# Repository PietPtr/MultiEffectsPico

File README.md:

# mep

Experiments for building a multi-effects processor on a Raspberry Pi Pico using I2S ADC's / DAC's and other IO for configuration

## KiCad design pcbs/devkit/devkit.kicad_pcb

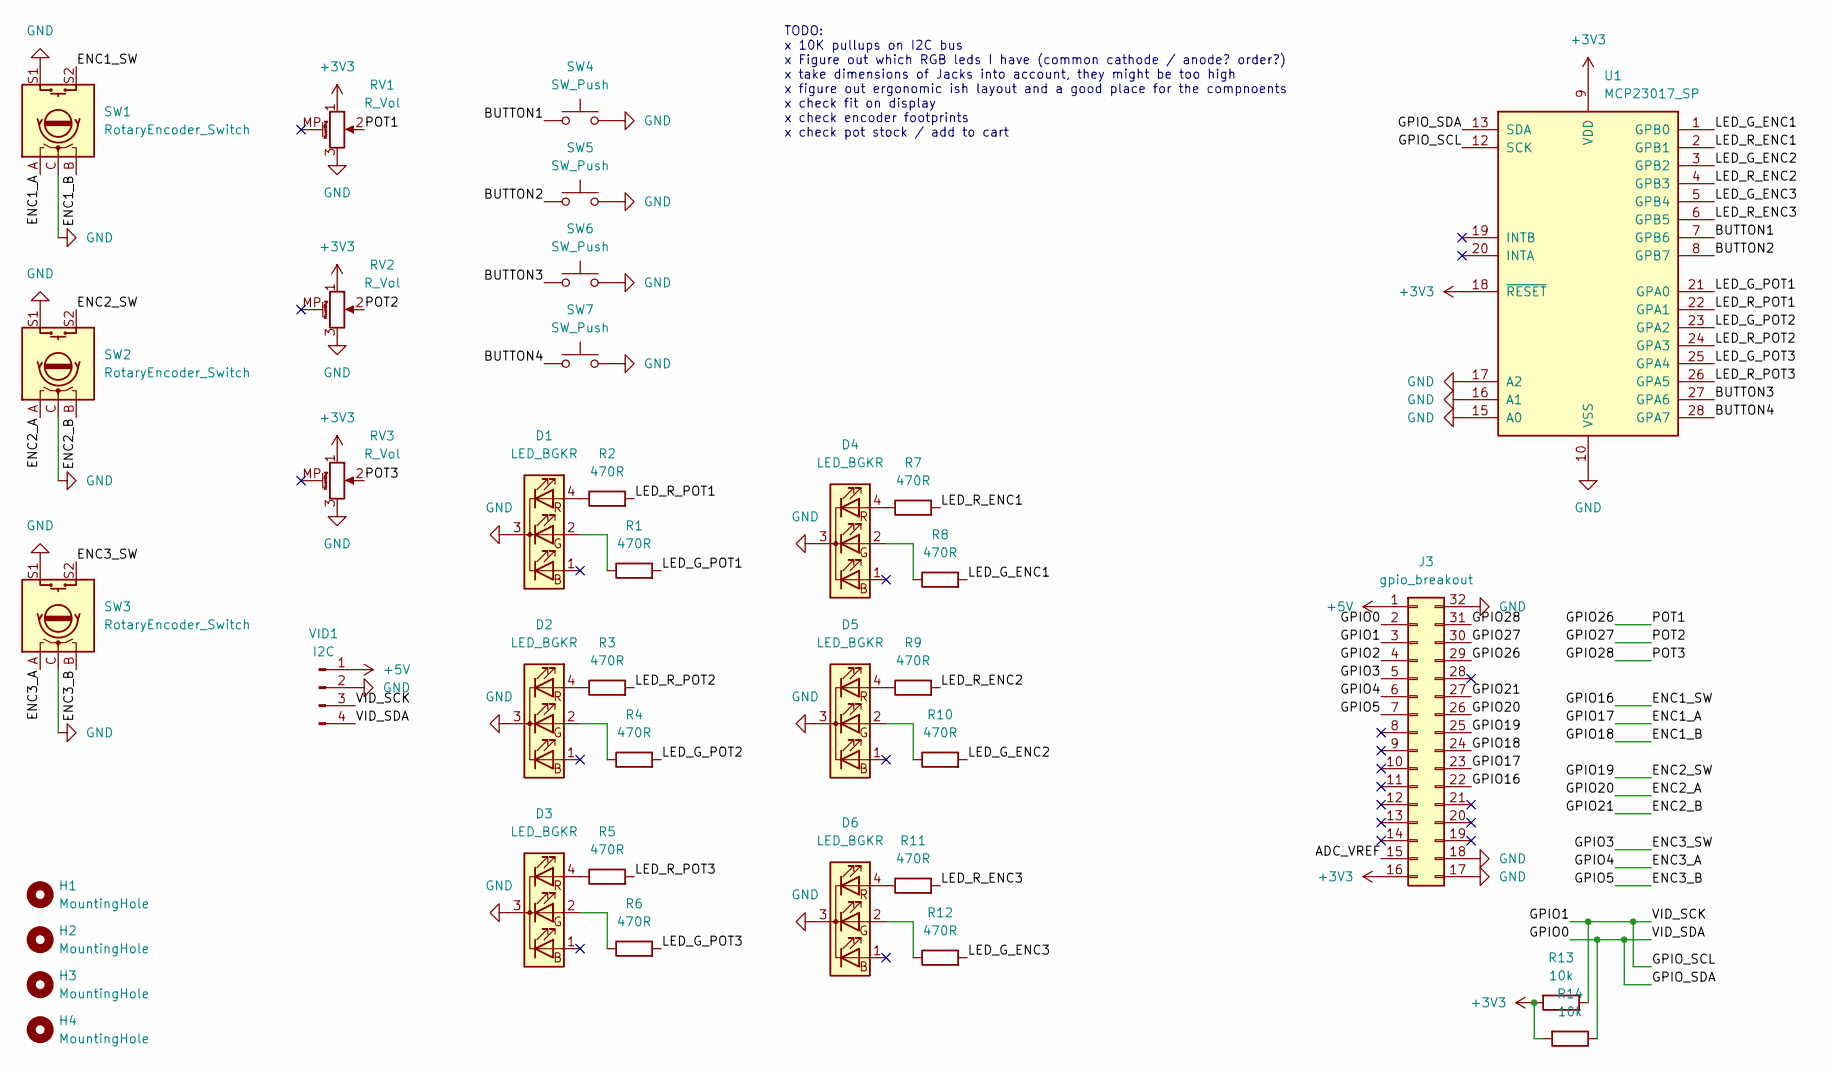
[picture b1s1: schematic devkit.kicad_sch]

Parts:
D1, D2, D3, D4, D5, D6: LED_BGKR; LED_D5.0mm-4_RGB
H1, H2, H3, H4: MountingHole; MountingHole_3.2mm_M3
J3: gpio_breakout; PinSocket_2x16_P2.54mm_Vertical
R1, R2, R3, R4, R5, R6, R7, R8, R9, R10, R11, R12: 470R; R_Axial_DIN0207_L6.3mm_D2.5mm_P7.62mm_Horizontal
R13, R14: 10k; R_Axial_DIN0207_L6.3mm_D2.5mm_P7.62mm_Horizontal
RV1, RV2, RV3: R_Vol; Potentiometer_Alps_RK09K_Single_Vertical
SW1, SW2, SW3: RotaryEncoder_Switch; RotaryEncoder_Alps_EC11E-Switch_Vertical_H20mm_MountingHoles
SW4, SW5, SW6, SW7: SW_Push; KAILH_MUTE
U1: MCP23017_SP; DIP-28_W7.62mm
VID1: I2C; PinHeader_1x04_P2.54mm_Vertical

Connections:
+3V3: J3.16, R13.2, R14.2, RV1.1, RV2.1, RV3.1, U1.9 (VDD), U1.18 (~RESET)
+5V: J3.1, VID1.1
/ADC_VREF: J3.15
/BUTTON1: SW4.1, U1.7 (GPB6)
/BUTTON2: SW5.1, U1.8 (GPB7)
/BUTTON3: SW6.1, U1.27 (GPA6)
/BUTTON4: SW7.1, U1.28 (GPA7)
/ENC1_A: J3.23, SW1.A
/ENC1_B: J3.24, SW1.B
/ENC1_SW: J3.22, SW1.S2
/ENC2_A: J3.26, SW2.A
/ENC2_B: J3.27, SW2.B
/ENC2_SW: J3.25, SW2.S2
/ENC3_A: J3.6, SW3.A
/ENC3_B: J3.7, SW3.B
/ENC3_SW: J3.5, SW3.S2
/GPIO0: J3.2, R14.1, U1.13 (SDA), VID1.4
/GPIO1: J3.3, R13.1, U1.12 (SCK), VID1.3
/GPIO2: J3.4
/GPIO26: J3.29, RV1.2
/GPIO27: J3.30, RV2.2
/GPIO28: J3.31, RV3.2
/LED_G_ENC1: R8.2, U1.1 (GPB0)
/LED_G_ENC2: R10.2, U1.3 (GPB2)
/LED_G_ENC3: R12.2, U1.5 (GPB4)
/LED_G_POT1: R1.2, U1.21 (GPA0)
/LED_G_POT2: R4.2, U1.23 (GPA2)
/LED_G_POT3: R6.2, U1.25 (GPA4)
/LED_R_ENC1: R7.2, U1.2 (GPB1)
/LED_R_ENC2: R9.2, U1.4 (GPB3)
/LED_R_ENC3: R11.2, U1.6 (GPB5)
/LED_R_POT1: R2.2, U1.22 (GPA1)
/LED_R_POT2: R3.2, U1.24 (GPA3)
/LED_R_POT3: R5.2, U1.26 (GPA5)
GND: D1.3 (K), D2.3 (K), D3.3 (K), D4.3 (K), D5.3 (K), D6.3 (K), J3.17, J3.18, J3.32, RV1.3, RV2.3, RV3.3, SW1.C, SW1.S1, SW2.C, SW2.S1, SW3.C, SW3.S1, SW4.2, SW5.2, SW6.2, SW7.2, U1.10 (VSS), U1.15 (A0), U1.16 (A1), U1.17 (A2), VID1.2
unnamed: D1.2 (GA), R1.1
unnamed: D1.4 (RA), R2.1
unnamed: D2.2 (GA), R4.1
unnamed: D2.4 (RA), R3.1
unnamed: D3.2 (GA), R6.1
unnamed: D3.4 (RA), R5.1
unnamed: D4.2 (GA), R8.1
unnamed: D4.4 (RA), R7.1
unnamed: D5.2 (GA), R10.1
unnamed: D5.4 (RA), R9.1
unnamed: D6.2 (GA), R12.1
unnamed: D6.4 (RA), R11.1

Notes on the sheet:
TODO: x 10K pullups on I2C bus x Figure out which RGB leds I have (common cathode / anode? order?) x take dimensions of Jacks into account, they might be too high x figure out ergonomic ish layout and a good place for the compnoents x check fit on display x check encoder footprints x check pot stoc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

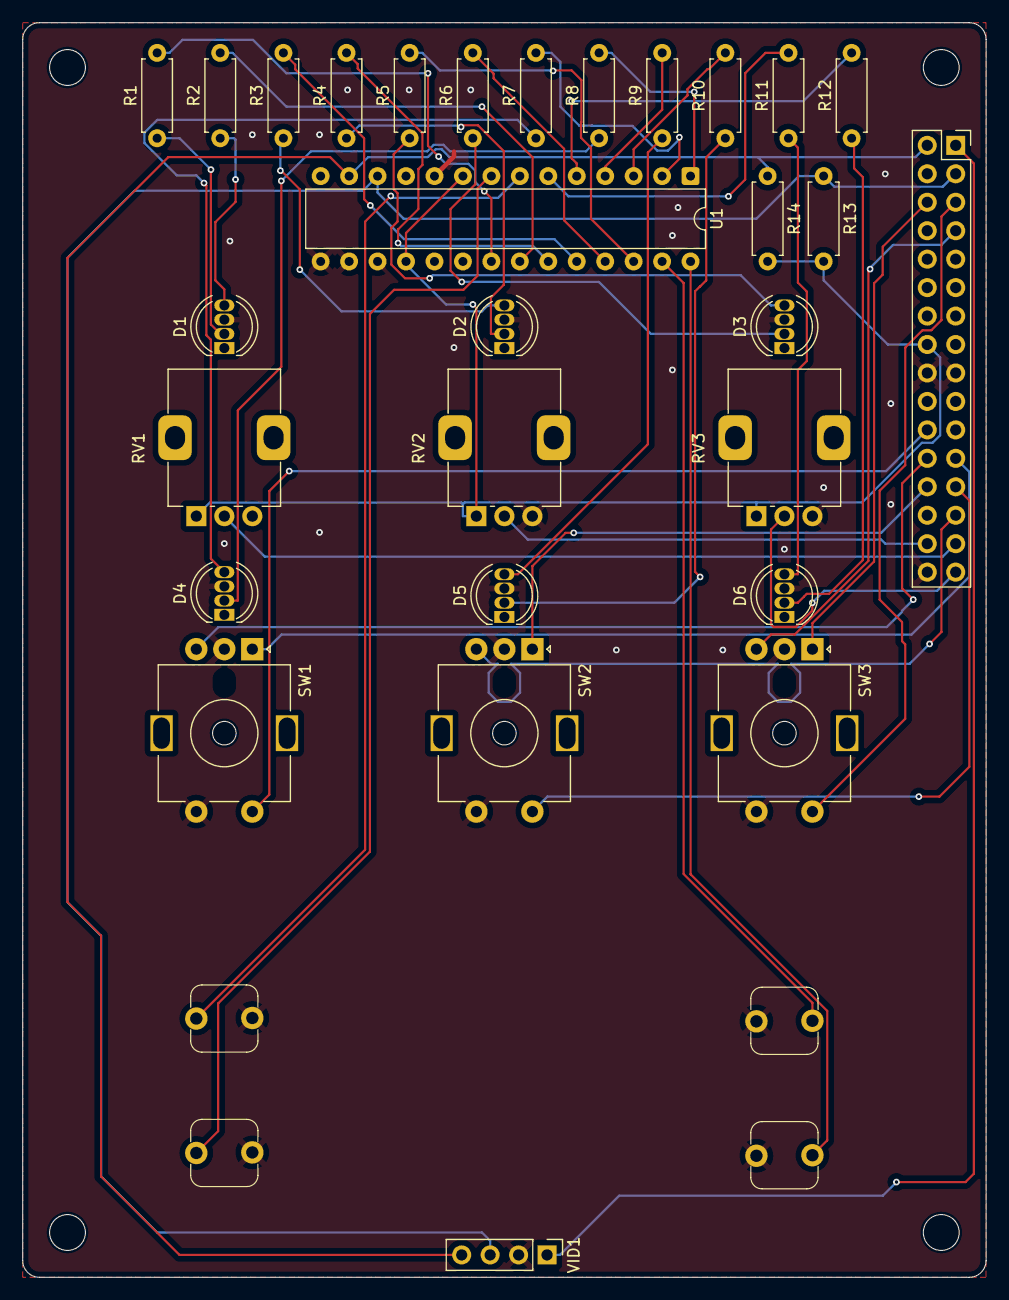
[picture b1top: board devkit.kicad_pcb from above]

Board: 2 copper layers, 86.0 x 112.0 mm, 37 parts (0 on the bottom side), 45 nets.

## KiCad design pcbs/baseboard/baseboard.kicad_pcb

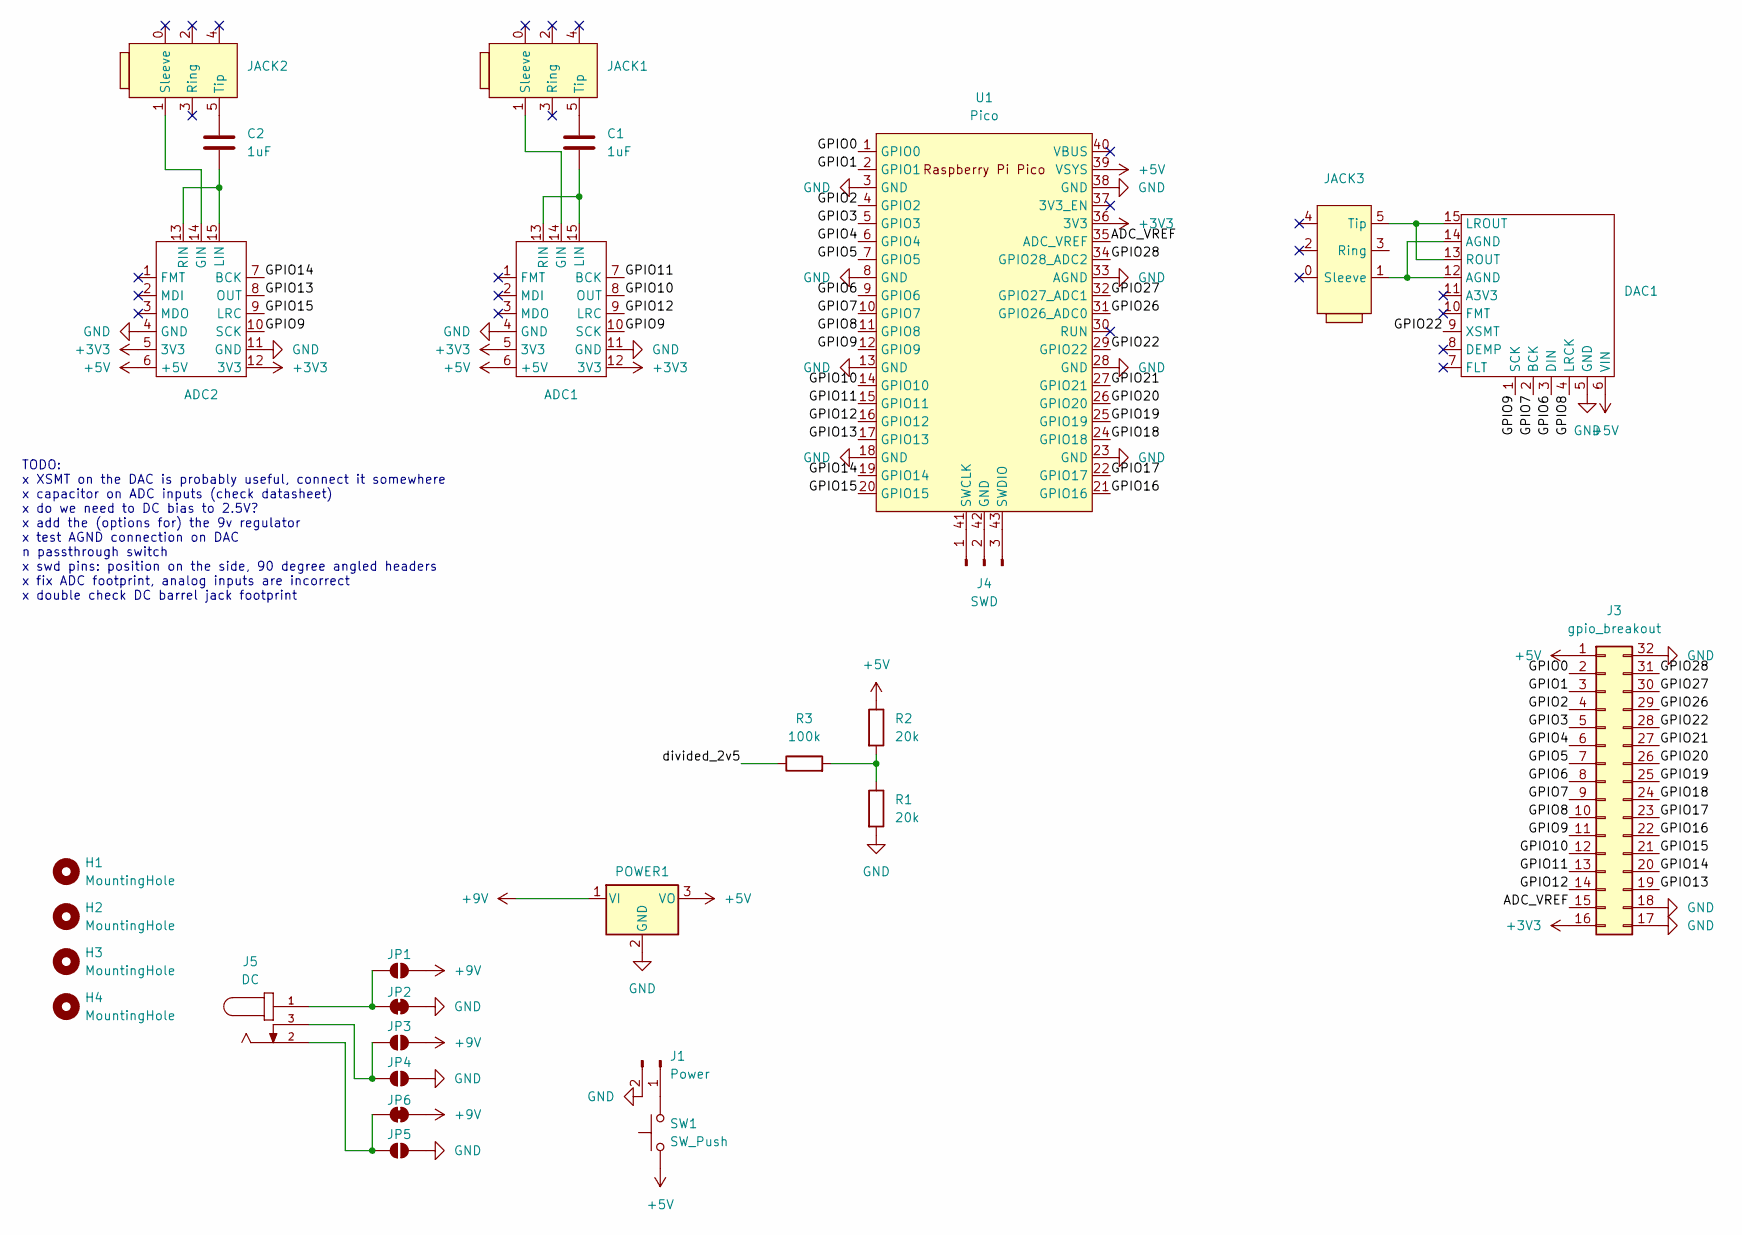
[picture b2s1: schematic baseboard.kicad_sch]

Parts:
ADC1, ADC2: PCM1808_breakout
C1, C2: 1uF; C_Radial_D5.0mm_H11.0mm_P2.00mm
DAC1: PCM5102_BREAKOUT
H1, H2, H3, H4: MountingHole; MountingHole_3.2mm_M3
J1: Power; PinHeader_1x02_P2.54mm_Vertical
J3: gpio_breakout; PinSocket_2x16_P2.54mm_Vertical
J4: SWD; PinHeader_1x03_P2.54mm_Vertical
J5: DC; GCT_DCJ200-10-A-XX-K_REVA; PARTREV A
JACK1, JACK2, JACK3: SlimJack6.3
JP1, JP3, JP4, JP5: SolderJumper-2_P1.3mm_Open_RoundedPad1.0x1.5mm
JP2, JP6: SolderJumper-2_P1.3mm_Bridged_RoundedPad1.0x1.5mm
POWER1: LM7805_TO220; TO-220-3_Horizontal_TabDown
R1, R2: 20k; R_Axial_DIN0207_L6.3mm_D2.5mm_P7.62mm_Horizontal
R3: 100k; R_Axial_DIN0207_L6.3mm_D2.5mm_P7.62mm_Horizontal
SW1: SW_Push; PinHeader_1x03_P2.54mm_Vertical
U1: Pico; RPi_Pico_SMD_TH

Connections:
+3V3: ADC1.5 (3V3), ADC1.12 (3V3), ADC2.5 (3V3), ADC2.12 (3V3), J3.16, U1.36 (3V3)
+5V: ADC1.6 (+5V), ADC2.6 (+5V), DAC1.6 (VIN), J3.1, POWER1.3 (VO), R2.1, SW1.1, U1.39 (VSYS)
+9V: JP1.2 (B), JP3.2 (B), JP6.2 (B), POWER1.1 (VI)
/ADC_VREF: J3.15, U1.35 (ADC_VREF)
/GPIO0: J3.2, U1.1 (GPIO0)
/GPIO1: J3.3, U1.2 (GPIO1)
/GPIO2: J3.4, U1.4 (GPIO2)
/GPIO3: J3.5, U1.5 (GPIO3)
/GPIO4: J3.6, U1.6 (GPIO4)
/GPIO5: J3.7, U1.7 (GPIO5)
/GPIO6: DAC1.3 (DIN), J3.8, U1.9 (GPIO6)
/GPIO7: DAC1.2 (BCK), J3.9, U1.10 (GPIO7)
/GPIO8: DAC1.4 (LRCK), J3.10, U1.11 (GPIO8)
/GPIO9: ADC1.10 (SCK), ADC2.10 (SCK), DAC1.1 (SCK), J3.11, U1.12 (GPIO9)
/GPIO10: ADC1.8 (OUT), J3.12, U1.14 (GPIO10)
/GPIO11: ADC1.7 (BCK), J3.13, U1.15 (GPIO11)
/GPIO12: ADC1.9 (LRC), J3.14, U1.16 (GPIO12)
/GPIO13: ADC2.8 (OUT), J3.19, U1.17 (GPIO13)
/GPIO14: ADC2.7 (BCK), J3.20, U1.19 (GPIO14)
/GPIO15: ADC2.9 (LRC), J3.21, U1.20 (GPIO15)
/GPIO16: J3.22, U1.21 (GPIO16)
/GPIO17: J3.23, U1.22 (GPIO17)
/GPIO18: J3.24, U1.24 (GPIO18)
/GPIO19: J3.25, U1.25 (GPIO19)
/GPIO20: J3.26, U1.26 (GPIO20)
/GPIO21: J3.27, U1.27 (GPIO21)
/GPIO22: DAC1.9 (XSMT), J3.28, U1.29 (GPIO22)
/GPIO26: J3.29, U1.31 (GPIO26_ADC0)
/GPIO27: J3.30, U1.32 (GPIO27_ADC1)
/GPIO28: J3.31, U1.34 (GPIO28_ADC2)
/divided_2v5: R3.1
GND: ADC1.4 (GND), ADC1.11 (GND), ADC2.4 (GND), ADC2.11 (GND), DAC1.5 (GND), J1.2, J3.17, J3.18, J3.32, JP2.2 (B), JP4.2 (B), JP5.2 (B), POWER1.2 (GND), R1.2, U1.3 (GND), U1.8 (GND), U1.13 (GND), U1.18 (GND), U1.23 (GND), U1.28 (GND), U1.33 (AGND), U1.38 (GND)
unnamed: ADC1.14 (GIN), JACK1.1 (Sleeve)
unnamed: ADC1.13 (RIN), ADC1.15 (LIN), C1.2
unnamed: ADC2.14 (GIN), JACK2.1 (Sleeve)
unnamed: ADC2.13 (RIN), ADC2.15 (LIN), C2.2
unnamed: DAC1.13 (ROUT), DAC1.15 (LROUT), JACK3.5 (Tip)
unnamed: J1.1, SW1.2
unnamed: J4.1, U1.41 (SWCLK)
unnamed: J4.2, U1.42 (GND)
unnamed: J4.3, U1.43 (SWDIO)
unnamed: C1.1, JACK1.5 (Tip)
unnamed: C2.1, JACK2.5 (Tip)
unnamed: DAC1.12 (AGND), DAC1.14 (AGND), JACK3.1 (Sleeve)
unnamed: J5.1, JP1.1 (A), JP2.1 (A)
unnamed: J5.3, JP3.1 (A), JP4.1 (A)
unnamed: J5.2, JP5.1 (A), JP6.1 (A)
unnamed: R1.1, R2.2, R3.2

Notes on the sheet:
TODO: x XSMT on the DAC is probably useful, connect it somewhere x capacitor on ADC inputs (check datasheet) x do we need to DC bias to 2.5V? x add the (options for) the 9v regulator x test AGND connection on DAC n passthrough switch x swd pins: position on the side, 90 degree angled headers x fix 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

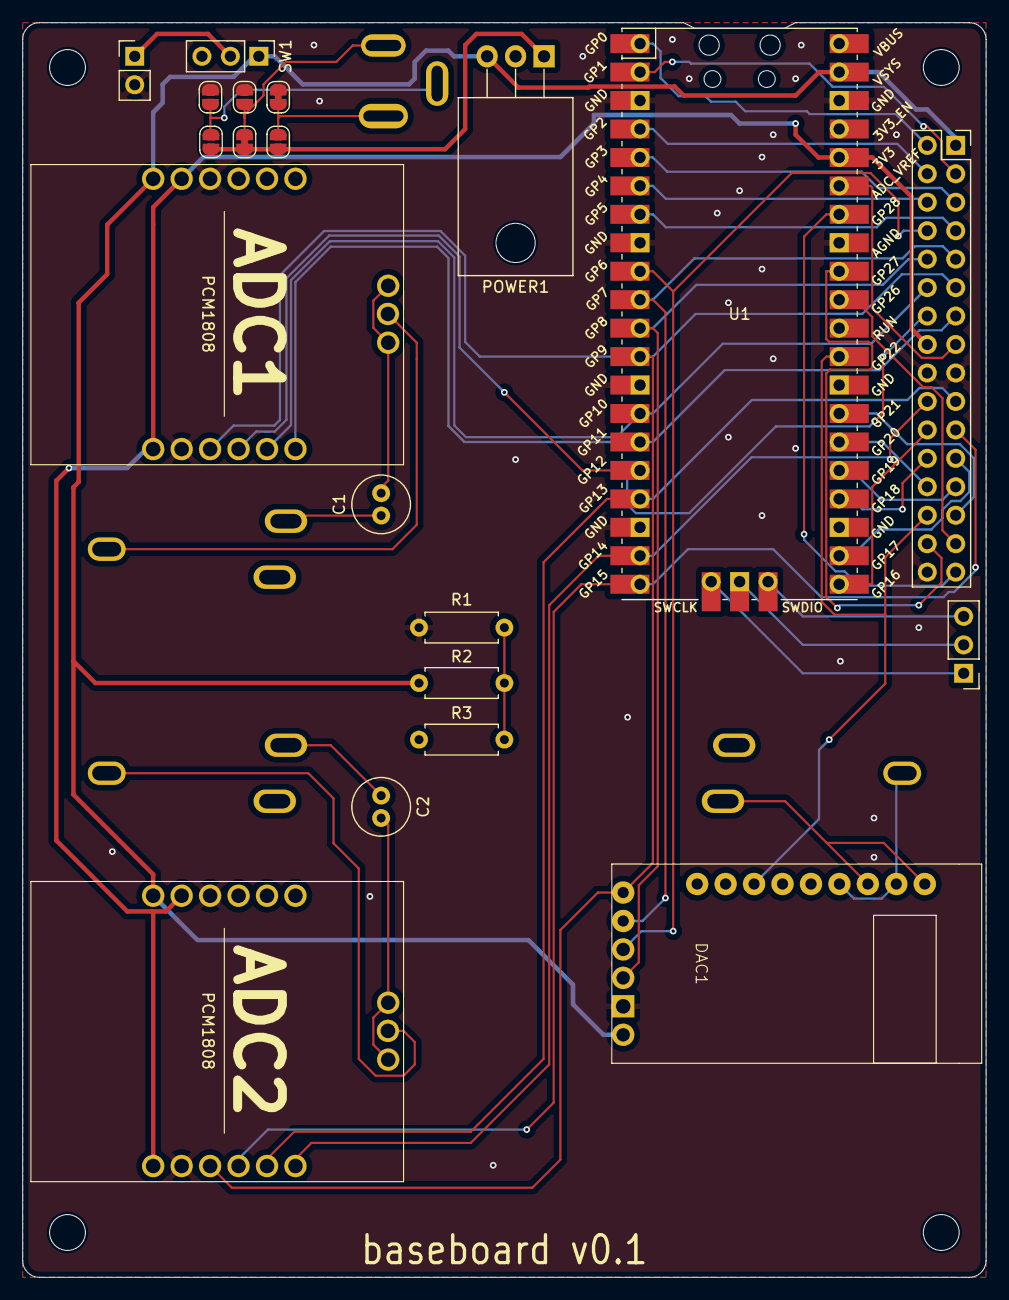
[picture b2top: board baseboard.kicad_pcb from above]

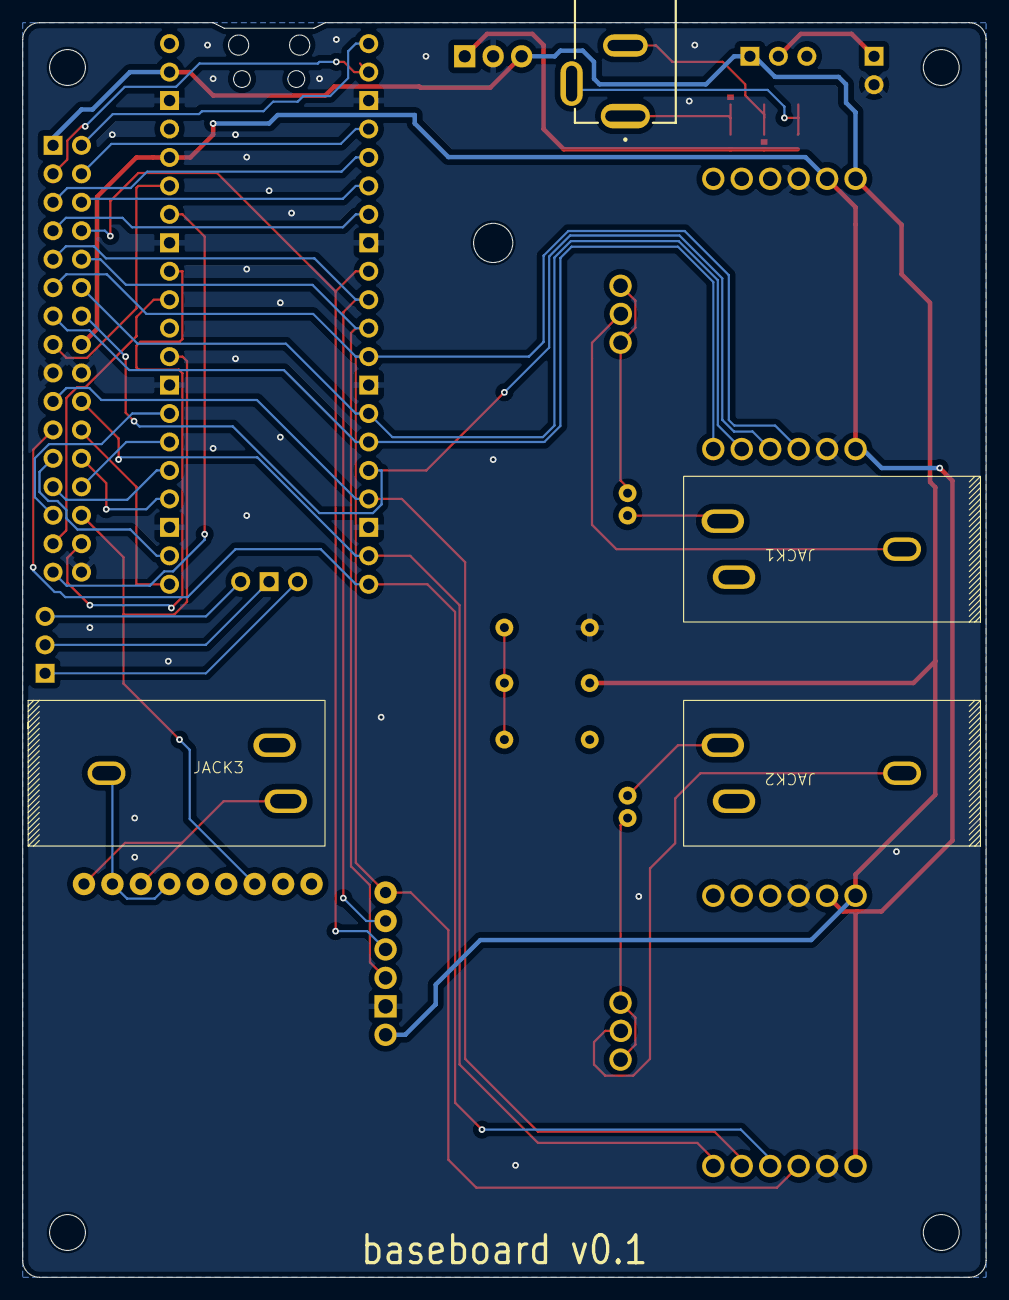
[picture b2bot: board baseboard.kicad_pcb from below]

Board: 2 copper layers, 86.0 x 112.0 mm, 28 parts (4 on the bottom side), 47 nets.

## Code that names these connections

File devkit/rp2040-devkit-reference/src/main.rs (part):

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
    // -- move to lib --

    let sck_pin: gpio::Pin<gpio::bank0::Gpio9, gpio::FunctionPio0, gpio::PullDown> =
        pins.gpio9.reconfigure();
    {
        #[rustfmt::skip]
        let sck_pio_program = pio_proc::pio_asm!(
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        &mut pio0,
        rp2040_i2s::PioClockDivider::FromSystemClock(sys_freq),
        sm0,
        pins.gpio6,
        pins.gpio7,
        pins.gpio8,
    )
    .unwrap();

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        &mut pio0,
        rp2040_i2s::PioClockDivider::FromSystemClock(sys_freq),
        sm1,
        pins.gpio10,
        pins.gpio11,
        pins.gpio12,
    )
    .unwrap();

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        &mut pio0,
        rp2040_i2s::PioClockDivider::FromSystemClock(sys_freq),
        sm2,
        pins.gpio13,
        pins.gpio14,
        pins.gpio15,
    )
    .unwrap();

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    info!("Start I/O thread.");

    let encoder1 = RotaryEncoder::new(
        pins.gpio17.into_pull_up_input().into_dyn_pin(),
        pins.gpio18.into_pull_up_input().into_dyn_pin(),
    )
    .into_standard_mode();
    let encoder2 = RotaryEncoder::new(
        pins.gpio20.into_pull_up_input().into_dyn_pin(),
        pins.gpio21.into_pull_up_input().into_dyn_pin(),
    )
    .into_standard_mode();
    let encoder3 = RotaryEncoder::new(
        pins.gpio4.into_pull_up_input().into_dyn_pin(),
        pins.gpio5.into_pull_up_input().into_dyn_pin(),
    )
    .into_standard_mode();

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    });

    let mut pot_readers: [AdcPin<Pin<DynPinId, DynFunction, PullDown>>; 3] = [
        AdcPin::new(pins.gpio26.reconfigure().into_dyn_pin()).unwrap(),
        AdcPin::new(pins.gpio27.reconfigure().into_dyn_pin()).unwrap(),
        AdcPin::new(pins.gpio28.reconfigure().into_dyn_pin()).unwrap(),
    ];

    let mut adc = Adc::new(pac.ADC, &mut pac.RESETS);

    let i2c = I2C::i2c0(
        pac.I2C0,
        pins.gpio0.reconfigure(),
        pins.gpio1.reconfigure(),
        100.kHz(),
        &mut pac.RESETS,
        &clocks.system_clock,
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        .unwrap();

    let enc_switches: [Pin<DynPinId, FunctionSioInput, PullUp>; 3] = [
        pins.gpio16.reconfigure().into_dyn_pin(),
        pins.gpio19.reconfigure().into_dyn_pin(),
        pins.gpio3.reconfigure().into_dyn_pin(),
    ];

    let mut display: GraphicsMode<_> = sh1106::Builder::new()
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    ];
    let mut activity = 0;

    const BUTTON1_PIN: u8 = 6;
    const BUTTON2_PIN: u8 = 7;
    const BUTTON3_PIN: u8 = 14;
    const BUTTON4_PIN: u8 = 15;

    let mut freqmon = FrequencyMonitor::new(1);
    let mut scope = AudioScope::new();
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
    loop {
        // Read inputs (buttons, pots, encoders)
        if !io_expander.digital_read(BUTTON1_PIN).unwrap() {
            selected_menu = Menu::Tests
        }
        if !io_expander.digital_read(BUTTON2_PIN).unwrap() {
            selected_menu = Menu::FrequencyMonitor;
        }
        if !io_expander.digital_read(BUTTON3_PIN).unwrap() {
            selected_menu = Menu::AudioScope;
        }

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            pot_values[i] = read;
        }

        if !io_expander.digital_read(BUTTON4_PIN).unwrap() {
            write!(adc_text, "{}", 4).unwrap();
        }

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
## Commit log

2025-06-18 All three validations in passthrough work
2025-06-19 Add schema of baseboard PCB
2025-06-20 Add devkit and fingybass crates
2025-06-24 Expand baseboard + devkit
2025-06-25 Order baseboard and devkit
2025-07-19 Working distortion effect on dev kit
2025-07-19 Validate devkit and baseboard v0.1
2025-07-21 Start freqmon
2025-07-21 Add rp2040 cycle counter and freqmon benchmark
2025-07-23 Test freqmon
2025-07-23 Add audioscope
2025-07-25 Add prototype breath controller
2025-07-27 Test and expand audioscope
2025-07-29 MOve configurator, add test (not finished)
